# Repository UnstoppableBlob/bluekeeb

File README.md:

# Bluekeeb

A custom made low-profile mechanical keyboard that uses a XIAO seeed module as the controller, a master-slave implementation of the firmware, that uses ZMK. Hassles with batteries can be avoided, due to the battery management and charging systems of the XIAO module in use. I have made the decision to remove the row of function keys, and replace them with a rotary encoder on the right side that controls music volume, and on the left side, a rotary encoder that controls the brightness of your display.

## How I made this

I made this using the OPL Kicad Library, running Kicad 8.0 on Windows 11. I have compiled it all to a manufacturable gerbers.zip file containing all the important info. I have a rotary encoder, which I'm planning to use a standard, 11 millimeter ec11 rotary encoder. Along with that, I'm going to use Choc v1 Kailh key switches, paired with custom 3d-printed keycaps. 

## Why did I make this

I made it because I was bored, and then I ended up spending a lot of time on it I guess? Also to qualify for stasis.hackclub.com's hackathon in Austin, TX.

## Assembled PCB (without the case and keycaps)

## PCB

## Schematic

## Case + PCB + electronics

Actually, while I was using freecad, after I had the whole thing set up, It didn't let me export or import files, even though I was trying to import/export supported file formats. I was only able to get the case, rotary encoders, and the PCB to show up on the render. 

The newer case (Bluekeeb case.step, not bluekeeb.step) is a newer version of the case that I am going to print out myself, as well as ordering all the components myself. The cases has a slot open for the usb c cable connection coming from the XIAO module.

|                              |                      |                    |                         |             | shipping on pcb causes it to jump in price so much. Shipping costs $17.81                                                              |               |                                                                                                                                                                                                                                                                                     |                                                                   |
|------------------------------|----------------------|--------------------|-------------------------|-------------|----------------------------------------------------------------------------------------------------------------------------------------|---------------|-------------------------------------------------------------------------------------------------------------------------------------------------------------------------------------------------------------------------------------------------------------------------------------|-------------------------------------------------------------------|
| Item                         | Description          | Quantity           | Unit Price              | Total Price | Total (with tax & shipping incl.)                                                                                                      | Running Total | Link                                                                                                                                                                                                                                                                                |                                                                   |
| PCB                          | PCB from jlcpcb      | 5 (jlcpcb minimum) | $16.30                  | $16.30      | $36.41                                                                                                                                 | $36.41        | https://cart.jlcpcb.com/quote                                                                                                                                                                                                                                                       | Cheapest PCB quote I could find                                   |
| Kailh Choc v1 (70pcs)        | Low profile switches | 1                  | $18.25                  | $18.25      | $20.21                                                                                                                                 | $56.62        | https://www.ebay.com/itm/157157330062                                                                                                                                                                                                                                               | Cheaper than on AliExpress                                        |
| Seeed Studio XIAO nRF52840   | MCU                  | 2                  | $9.99                   | $19.98      | $22.39                                                                                                                                 | $79.01        | https://www.amazon.com/gp/product/B0C6Q67V97?smid=A1YZW40LYQY3L1&psc=1                                                                                                                                                                                                              | Cheaper than AliExpress including shipping using holiday discount |
|                              |                      |                    |                         |             | The Seeed Studio price is discounted by $5 (price includes discount). If I order after the 31st of December, the price will be $27.93. |               |                                                                                                                                                                                                                                                                                     |                                                                   |
| Hot Swaps (50pcs)            | Sockets for Choc v1s | 1                  | $5.50                   | $5.50       | (AliExpress)                                                                                                                           | $79.01        | https://www.aliexpress.us/item/3256806423843004.html?spm=a2g0o.cart.0.0.47a538daYBbt9U&mp=1&pdp_npi=5%40dis%21USD%21USD%2011.46%21USD%205.50%21%21USD%205.50%21%21%21%40210328db17669560346357255e1c7d%2112000037825583671%21ct%21US%216953170698%21%211%210&gatewayAdapt=glo2usa   |                                                                   |
| Hot Swaps (30pcs)            | Sockets for Choc v1s | 1                  | $0.99 welcome discount) | $0.99       | (AliExpress)                                                                                                                           | $79.01        | https://www.aliexpress.us/item/3256802980434588.html?spm=a2g0o.cart.0.0.47a538daYBbt9U&mp=1&pdp_npi=5%40dis%21USD%21USD%205.63%21USD%200.99%21%21USD%200.97%21%21%21%40210328db17669560346357255e1c7d%2112000024451955236%21ct%21US%216953170698%21%211%210&gatewayAdapt=glo2usa    |                                                                   |
| 1N4148W (100pcs)             | Diodes               | 1                  | $1.48                   | $1.48       | (AliExpress)                                                                                                                           | $79.01        | https://www.aliexpress.us/item/3256807716771073.html?spm=a2g0o.cart.0.0.47a538daYBbt9U&mp=1&pdp_npi=5%40dis%21USD%21USD%201.48%21USD%201.48%21%21USD%201.48%21%21%21%40210328db17669560346357255e1c7d%2112000042781108223%21ct%21US%216953170698%21%211%210&gatewayAdapt=glo2usa    |                                                                   |
| 3.7V LiPo batteries (2-pack) | 1000mah Battery      | 1                  | $10.66                  | $10.66      | $18.61 (total for AliExpress)                                                                                                          | $97.62        | https://www.aliexpress.us/item/3256803193874231.html?spm=a2g0o.cart.0.0.47a538datUX9yB&mp=1&pdp_npi=5%40dis%21USD%21USD%2015.23%21USD%2010.66%21%21USD%2010.66%21%21%21%402103126e17669575315265295e8fbd%2112000032368701982%21ct%21US%216953170698%21%211%210&gatewayAdapt=glo2usa |                                                                   |

(I will purchase all parts myself, all bits should be going toward qualification :))

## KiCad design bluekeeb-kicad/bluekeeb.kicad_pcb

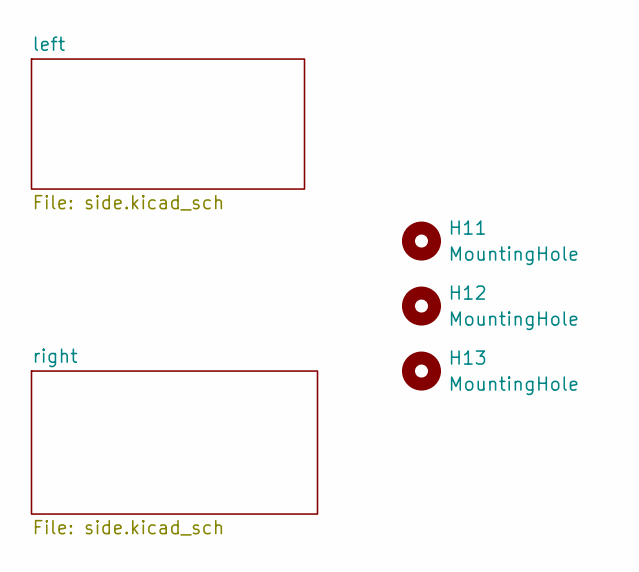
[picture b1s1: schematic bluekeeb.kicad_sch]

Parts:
H11, H12, H13: MountingHole; mouse-bite-5mm-slot

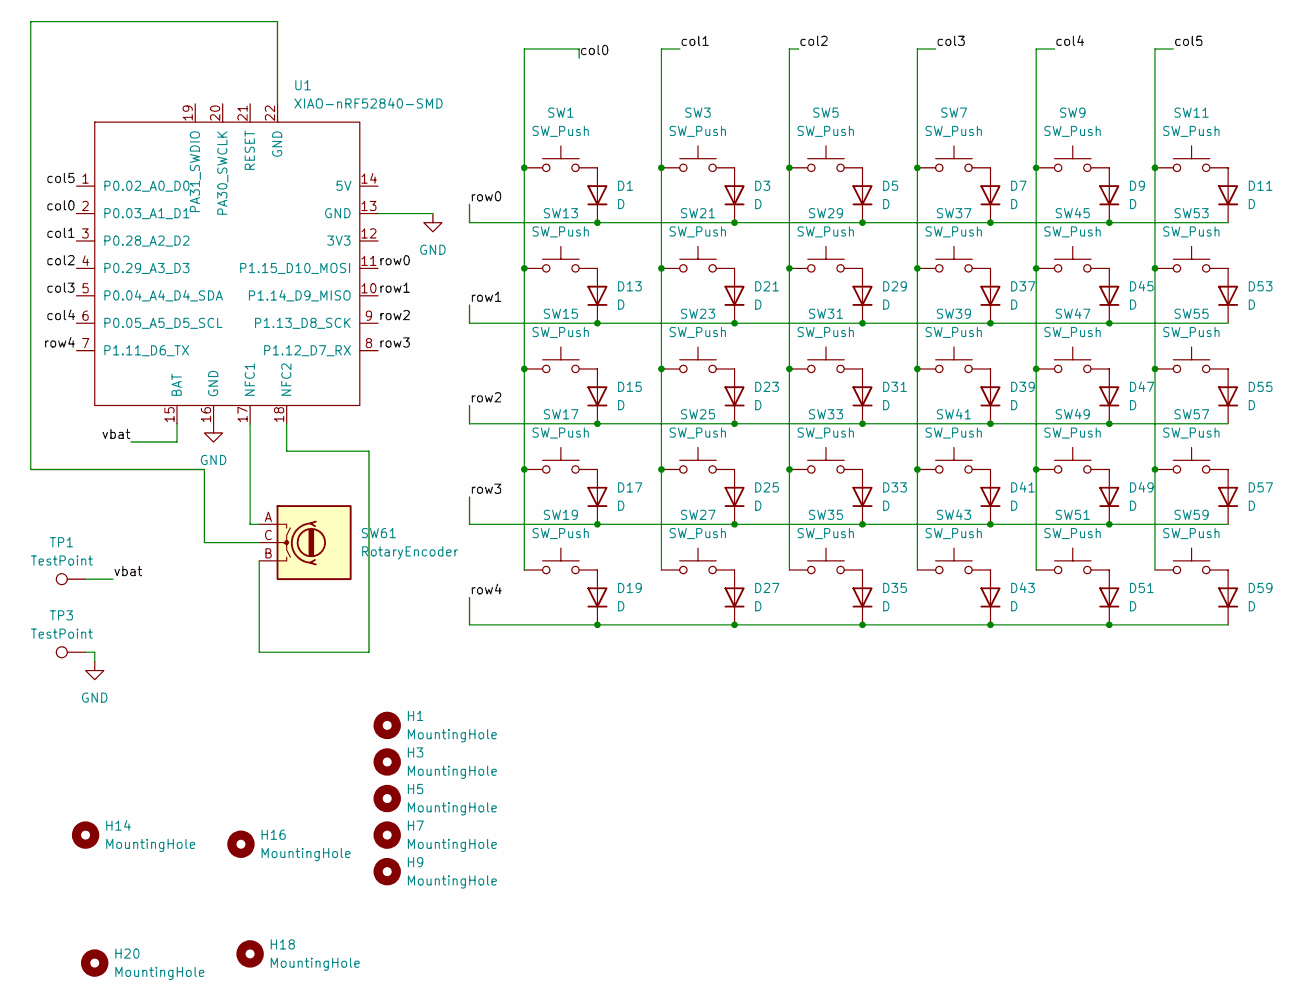
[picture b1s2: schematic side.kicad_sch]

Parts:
D1, D3, D5, D7, D9, D11, D13, D15, D17, D19, D21, D23, D25, D27, D29, D31, D33, D35, D37, D39, D41, D43, D45, D47, D49, D51, D53, D55, D57, D59: D; D_SOD-123
H1, H3, H5, H7, H9: MountingHole; mouse-bite-5mm-slot
H14, H16, H18, H20: MountingHole; MountingHole_2.2mm_M2
SW1, SW3, SW5, SW7, SW9, SW11, SW13, SW15, SW17, SW19, SW21, SW23, SW25, SW27, SW29, SW31, SW33, SW35, SW37, SW39, SW41, SW43, SW45, SW47, SW49, SW51, SW53, SW55, SW57, SW59: SW_Push; SW_choc_v1_HS_CPG135001S30_1u
SW61: RotaryEncoder; RotaryEncoder_Alps_EC11E-Switch_Vertical_H20mm
TP1, TP3: TestPoint; TestPoint_Pad_D2.0mm
U1: XIAO-nRF52840-SMD; modified-XIAO-nRF52840-SMD

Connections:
/left/col0: SW1.1, SW13.1, SW15.1, SW17.1, SW19.1, U1.2 (P0.03_A1_D1)
/left/col1: SW3.1, SW21.1, SW23.1, SW25.1, SW27.1, U1.3 (P0.28_A2_D2)
/left/col2: SW5.1, SW29.1, SW31.1, SW33.1, SW35.1, U1.4 (P0.29_A3_D3)
/left/col3: SW7.1, SW37.1, SW39.1, SW41.1, SW43.1, U1.5 (P0.04_A4_D4_SDA)
/left/col4: SW9.1, SW45.1, SW47.1, SW49.1, SW51.1, U1.6 (P0.05_A5_D5_SCL)
/left/col5: SW11.1, SW53.1, SW55.1, SW57.1, SW59.1, U1.1 (P0.02_A0_D0)
/left/row0: D1.1 (K), D3.1 (K), D5.1 (K), D7.1 (K), D9.1 (K), D11.1 (K), U1.11 (P1.15_D10_MOSI)
/left/row1: D13.1 (K), D21.1 (K), D29.1 (K), D37.1 (K), D45.1 (K), D53.1 (K), U1.10 (P1.14_D9_MISO)
/left/row2: D15.1 (K), D23.1 (K), D31.1 (K), D39.1 (K), D47.1 (K), D55.1 (K), U1.9 (P1.13_D8_SCK)
/left/row3: D17.1 (K), D25.1 (K), D33.1 (K), D41.1 (K), D49.1 (K), D57.1 (K), U1.8 (P1.12_D7_RX)
/left/row4: D19.1 (K), D27.1 (K), D35.1 (K), D43.1 (K), D51.1 (K), D59.1 (K), U1.7 (P1.11_D6_TX)
/left/vbat: TP1.1, U1.15 (BAT)
GND: TP3.1, U1.13 (GND), U1.16 (GND); also elsewhere on the board
unnamed: D1.2 (A), SW1.2
unnamed: D3.2 (A), SW3.2
unnamed: D5.2 (A), SW5.2
unnamed: D7.2 (A), SW7.2
unnamed: D9.2 (A), SW9.2
unnamed: D11.2 (A), SW11.2
unnamed: D13.2 (A), SW13.2
unnamed: D15.2 (A), SW15.2
unnamed: D17.2 (A), SW17.2
unnamed: D19.2 (A), SW19.2
unnamed: D21.2 (A), SW21.2
unnamed: D23.2 (A), SW23.2
unnamed: D25.2 (A), SW25.2
unnamed: D27.2 (A), SW27.2
unnamed: D29.2 (A), SW29.2
unnamed: D31.2 (A), SW31.2
unnamed: D33.2 (A), SW33.2
unnamed: D35.2 (A), SW35.2
unnamed: D37.2 (A), SW37.2
unnamed: D39.2 (A), SW39.2
unnamed: D41.2 (A), SW41.2
unnamed: D43.2 (A), SW43.2
unnamed: D45.2 (A), SW45.2
unnamed: D47.2 (A), SW47.2
unnamed: D49.2 (A), SW49.2
unnamed: D51.2 (A), SW51.2
unnamed: D53.2 (A), SW53.2
unnamed: D55.2 (A), SW55.2
unnamed: D57.2 (A), SW57.2
unnamed: D59.2 (A), SW59.2
unnamed: SW61.C, U1.22 (GND)
unnamed: SW61.A, U1.17 (NFC1)
unnamed: SW61.B, U1.18 (NFC2)

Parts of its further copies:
D2, D4, D6, D8, D10, D12, D14, D16, D18, D20, D22, D24, D26, D28, D30, D32, D34, D36, D38, D40, D42, D44, D46, D48, D50, D52, D54, D56, D58, D60: D; D_SOD-123
H15, H17, H19: MountingHole; MountingHole_2.2mm_M2
SW2, SW4, SW6, SW8, SW10, SW12, SW14, SW16, SW18, SW20, SW22, SW24, SW26, SW28, SW30, SW32, SW34, SW36, SW38, SW40, SW42, SW44, SW46, SW48, SW50, SW52, SW54, SW56, SW58, SW60: SW_Push; SW_choc_v1_HS_CPG135001S30_1u
SW62: RotaryEncoder; RotaryEncoder_Alps_EC11E-Switch_Vertical_H20mm
TP2, TP4: TestPoint; TestPoint_Pad_D2.0mm
U2: XIAO-nRF52840-SMD; modified-XIAO-nRF52840-SMD

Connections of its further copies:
/right/col0: SW2.1, SW14.1, SW16.1, SW18.1, SW20.1, U2.2 (P0.03_A1_D1)
/right/col1: SW4.1, SW22.1, SW24.1, SW26.1, SW28.1, U2.3 (P0.28_A2_D2)
/right/col2: SW6.1, SW30.1, SW32.1, SW34.1, SW36.1, U2.4 (P0.29_A3_D3)
/right/col3: SW8.1, SW38.1, SW40.1, SW42.1, SW44.1, U2.5 (P0.04_A4_D4_SDA)
/right/col4: SW10.1, SW46.1, SW48.1, SW50.1, SW52.1, U2.6 (P0.05_A5_D5_SCL)
/right/col5: SW12.1, SW54.1, SW56.1, SW58.1, SW60.1, U2.1 (P0.02_A0_D0)
/right/row0: D2.1 (K), D4.1 (K), D6.1 (K), D8.1 (K), D10.1 (K), D12.1 (K), U2.11 (P1.15_D10_MOSI)
/right/row1: D14.1 (K), D22.1 (K), D30.1 (K), D38.1 (K), D46.1 (K), D54.1 (K), U2.10 (P1.14_D9_MISO)
/right/row2: D16.1 (K), D24.1 (K), D32.1 (K), D40.1 (K), D48.1 (K), D56.1 (K), U2.9 (P1.13_D8_SCK)
/right/row3: D18.1 (K), D26.1 (K), D34.1 (K), D42.1 (K), D50.1 (K), D58.1 (K), U2.8 (P1.12_D7_RX)
/right/row4: D20.1 (K), D28.1 (K), D36.1 (K), D44.1 (K), D52.1 (K), D60.1 (K), U2.7 (P1.11_D6_TX)
/right/vbat: TP2.1, U2.15 (BAT)
GND: TP4.1, U2.13 (GND), U2.16 (GND); also elsewhere on the board
unnamed: D2.2 (A), SW2.2
unnamed: D4.2 (A), SW4.2
unnamed: D6.2 (A), SW6.2
unnamed: D8.2 (A), SW8.2
unnamed: D10.2 (A), SW10.2
unnamed: D12.2 (A), SW12.2
unnamed: D14.2 (A), SW14.2
unnamed: D16.2 (A), SW16.2
unnamed: D18.2 (A), SW18.2
unnamed: D20.2 (A), SW20.2
unnamed: D22.2 (A), SW22.2
unnamed: D24.2 (A), SW24.2
unnamed: D26.2 (A), SW26.2
unnamed: D28.2 (A), SW28.2
unnamed: D30.2 (A), SW30.2
unnamed: D32.2 (A), SW32.2
unnamed: D34.2 (A), SW34.2
unnamed: D36.2 (A), SW36.2
unnamed: D38.2 (A), SW38.2
unnamed: D40.2 (A), SW40.2
unnamed: D42.2 (A), SW42.2
unnamed: D44.2 (A), SW44.2
unnamed: D46.2 (A), SW46.2
unnamed: D48.2 (A), SW48.2
unnamed: D50.2 (A), SW50.2
unnamed: D52.2 (A), SW52.2
unnamed: D54.2 (A), SW54.2
unnamed: D56.2 (A), SW56.2
unnamed: D58.2 (A), SW58.2
unnamed: D60.2 (A), SW60.2
unnamed: SW62.C, U2.22 (GND)
unnamed: SW62.A, U2.17 (NFC1)
unnamed: SW62.B, U2.18 (NFC2)

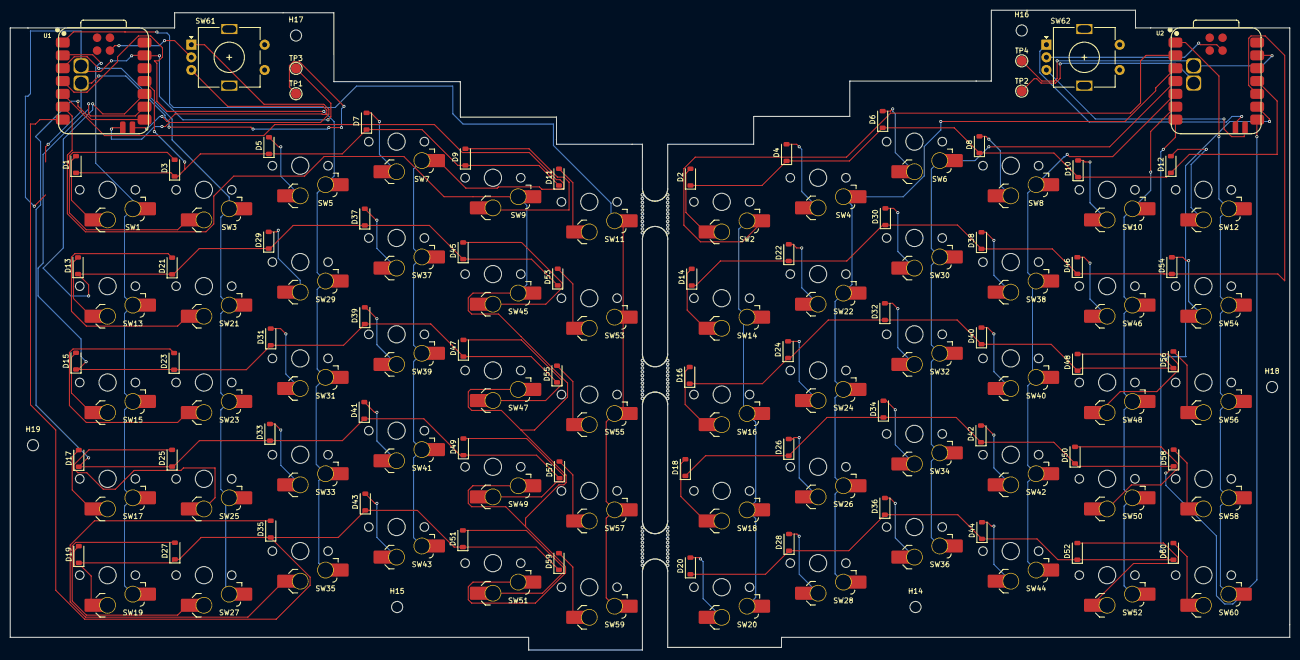
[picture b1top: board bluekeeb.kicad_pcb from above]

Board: 2 copper layers, 253.0 x 126.5 mm, 137 parts (0 on the bottom side), 91 nets.

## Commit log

2025-12-14 save
2025-12-14 Found an issue with pcb placement, started fixing
    i had an error with windows 11 and unix file endings, and couldn't figure out how to make a git repo until not too long ago, so that's why my initial commit has a lot of stuff on it.
2025-12-14 save before plugin
2025-12-14 save after kicad cntrl + s
2025-12-14 save before GND fix
2025-12-14 Finished pcb
2025-12-16 Finalllyyy i fixed my mousebites problem
2025-12-16 save (last commit wasn't with the project fully up-to-date)
2025-12-18 didn't commit for a long time, look at description.
    went to grabcad, found 3d models for everything, finished pcb with heal shapes, and then i started the modelling process.
2025-12-19 added some mounting holes, and i moved the testpoints to a different location.
2025-12-20 got the pcb ready for manufacturing
2025-12-25 add readme
    Added detailed project description and images.
2025-12-25 finished?
2025-12-28 Add case and PCB design information to README
    Added a section about the case and PCB design considerations.
2025-12-30 Fixed BOM
2026-04-25 added firmware
2026-04-25 added the new case
2026-04-25 update the readme
2026-04-25 add in the ino explanation
2026-04-26 added a full render, organised github
2026-04-27 added images
2026-04-27 readme change
2026-04-29 change bom
